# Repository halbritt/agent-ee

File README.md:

# agent-ee

**agent-ee turns a captured electronics design into a verified, native KiCad
project and a fabrication package, with tool evidence at every stage.** It is
being built as the engine of an AI-driven PCB generator: an agent and an
engineer settle requirements, parts and circuit intent, and agent-ee produces
the schematic, places and routes the board, runs the checks, and exports
Gerbers, drills, BOM and CPL. The same checks and independent-review machinery
also review and repair existing KiCad projects, which is where the project
started.

For explicit board and circuit decisions, use [design capture and compile](docs/design-compile.md), then [build run](docs/build-workflow.md). For end-user and operator guides, see the [Quickstart Guide](docs/quickstart.md), [Operator Runbook](docs/operator-runbook.md), [Architecture & Pipeline Guide](docs/architecture-pipeline.md), [Benchmarking Guide](docs/benchmarking-guide.md), and [Troubleshooting & FAQ](docs/troubleshooting-faq.md). Core terminology is documented in [GLOSSARY.md](GLOSSARY.md).

The owner's direction since 2026-10-17 is the generator
([decisions](docs/decisions.md)); the review workflow is one of its stages,
not the product. This README describes what the generator can do today and
what it cannot. The ticket-by-ticket history of implemented capabilities up to
2026-10-25 is in the [capability log](docs/capability-log.md), a frozen record.

How its placement and routing compare with stock KiCadRoutingTools on real
boards is measured in the
[matched benchmark](docs/benchmarks/krt-matched-2026-11-09.md). Its newest
"Result in brief" section is the current standing; it does not support a
general claim that agent-ee is better.

## Status at a glance (2026-11-14)

What works through the build entrypoint, `agent-ee build run`, and the synthesis entrypoint, `agent-ee design generate`:

| Stage | What runs | Demonstrated on |
| --- | --- | --- |
| Requirements & Synthesis | `design generate` turns prose requirements (`REQUIREMENTS.md`) into an `agent-ee.design/1` statement with trace citations via a subscription author seat; `build run` validates an authored spec, its byte-located requirement record and requirement-to-check map | `design generate`: led-flasher, load-switch, rs485 (benchmark r5b); `build run`: 17-part acquisition board |
| Parts | Binds authored/selected parts, captured datasheets, symbols and footprints to circuit intent; checks footprint DFM rules | acquisition board; generated r5b designs |
| Scaffold | Creates native project, board outline, stackup, rules and fixed connectors | acquisition board; generated r5b designs |
| Schematic | Emits native schematic from circuit intent, runs ERC and forward-annotates footprints | acquisition board; 130-part emitter benchmark; generated r5b designs |
| Placement and routing | Rust placement search over declared groups, fixed poses, locality and planes; routing by [kicad-route](docs/routing-adapter.md) at the commit each attempt records; native DRC and locality checks on the saved board | acquisition board; generated r5b designs; esp_prog (placement and routing only) |
| Artwork | Moves silk reference fields off conflicts under a receipt; places silkscreen labels | acquisition board; generated r5b designs |
| Package | Checks-only review (ERC, DRC, parity, interval, SPICE, DFM, assembly readiness, copper width), then Gerber/drill/BOM/CPL export bound to final board hash | acquisition board; generated r5b designs |

One real pre-authored design has completed all seven stages to an accepted package: the
17-part TPS7A20 + ADS1115 acquisition board, on 2026-10-24
([acceptance map](docs/system-acceptance.md)). In autonomous requirements-to-board
generation (`agent-ee design generate`), benchmark round r5b (2026-11-04) accepted
three of five boards (`led-flasher`, `load-switch`, `rs485`) from natural-language
requirements briefs; the two unaccepted boards (`current-monitor` and `usb-regulator`)
exposed tool defects (unpaired differential net handling, and pre-existing footprint
NPTH hole clearances) that were subsequently resolved in tooling. Subsequent
engineering reviews of the accepted boards identified design omissions (such as
unterminated bus failsafe bias and unbuffered off-board control inputs), which were
mapped to general check rules rather than board-specific fixes.

How placement and routing compare with stock KiCadRoutingTools on real boards is
measured in the [matched benchmark](docs/benchmarks/krt-matched-2026-11-09.md):
placing and routing on its own, agent-ee delivers 2 of 6 boards clean (and stock
KRT delivers 1 of 6); routing the designer's placement, the two are level.

Current pipeline capabilities and limitations:

- **Prose synthesis is provided by `agent-ee design generate`, not `build run`.**
  `agent-ee build run` requires structured JSON and Markdown inputs authored before
  the run. `agent-ee design generate` accepts prose requirements up to 32 KiB and
  queries an LLM author seat (`codex:gpt-6.1-sol:high` or `agy`) to synthesize
  `agent-ee.design/1` statements with quoted trace citations before compiling and
  building the candidate.
- **Build and routing times depend on search budgets.** Typical placement and
  routing passes require several to tens of minutes depending on board density and
  seed count; claims of "manufacturing-ready in under five minutes" do not describe
  non-trivial boards.
- **Functional-group and proximity intent are soft.** They steer the placement
  search as cost terms. Final acceptance checks declared pin locality, fixed
  connector edges, planes and native DRC; it does not check that every part
  landed in its group.
- **Engineering verification is as good as the authored map.** Only checks the
  map names are run; the mandatory set is ERC, DRC, netlist, geometry, parts
  membership, placement, envelope, fab profile, assembly readiness and package.
- **Automated testing runs on the host.** Host-native tests run via `mise` with
  Bubblewrap sandboxing; the full suite runs nightly on the host. Hosted CI
  validates commit recency rather than running tests or building images. Sample
  tables in documentation (such as the "21/25" PCBSchemaGen summary in the
  benchmarking guide) illustrate schema output formats, not verified measurements.
- **Independent AI review is not part of the build.** The package stage runs
  automated checks only. The review and campaign commands provide reviewers and
  adjudication for a candidate separately.

## How a build works

```text
spec.md + spec-record.json + requirement-map.json      (authored)
parts.json + circuit.json + layout.json + ratings.json (authored, captured sources)
envelope.json + fab-profile.json                       (authored)
placement.json + groups.json + planes.json             (authored)
        |
        v
agent-ee build run build.json --out RUN
  01 requirements  -> scope with mapped checks and accounting
  02 parts         -> bound connectivity intent and ratings receipt
  03 scaffold      -> empty native project with outline, stackup, rules, fixed parts
  04 schematic     -> .kicad_sch, ERC, netlist, footprints on the board
  05 placement-routing -> Rust placement search, kicad-route routing, saved-board DRC
  06 artwork       -> silk field relocation under receipt
  07 package       -> checks-only review, Gerbers/drills/BOM/CPL bound to board hash
```

Each stage writes a hash-bound candidate directory and a receipt. Resumption
re-checks the plan, the input source and the native tool runtime (KiCad, Python).
A changed agent-ee source does not refuse a resume; the report records it in
`tool_changes`. A `CANCEL` file stops before the next
stage. `--through STAGE` stops at a checkpoint for diagnosis. See the
[build workflow](docs/build-workflow.md) for the plan format and
[placement job](docs/placement-job.md) for search, router and budget settings.

### Core generator commands

| Command | Purpose | Reference |
| --- | --- | --- |
| `agent-ee build run PLAN` | Run the complete 7-stage generative build pipeline | [build-workflow](docs/build-workflow.md) |
| `agent-ee build review RUN` | Independently re-check completed build candidate | [build-workflow](docs/build-workflow.md) |
| `agent-ee place run CONFIG` | Execute standalone placement search and routing | [placement-job](docs/placement-job.md) |
| `agent-ee place metrics BOARD` | Evaluate native placement quality metrics and wirelengths | [placement-job](docs/placement-job.md) |
| `agent-ee parts compile ARGS` | Compile part selections and bind footprint/symbol sources | [parts-stage](docs/parts-stage.md) |
| `agent-ee design compile DESIGN` | Validate and compile typed design statement to build bundle | [design-compile](docs/design-compile.md) |
| `agent-ee design capture DESIGN` | Capture circuit and envelope into design schema | [design-compile](docs/design-compile.md) |
| `agent-ee design generate REQUIREMENTS` | Synthesize design schema statement from engineering requirements document | [design-compile](docs/design-compile.md) |
| `agent-ee design benchmark REQUIREMENTS_DIR` | Run automated benchmark suite across requirements documents | [benchmarking-guide](docs/benchmarking-guide.md) |

## Try it

The demonstrated environment is Linux with a KiCad 10.x release (including the
`pcbnew` Python bindings on the system interpreter), ngspice, Bubblewrap and
the Rust placement engine built from `crates/placement-engine`. The CLI has no
third-party Python dependencies. See [installation](docs/installation.md);
the installer links the source launcher `bin/agent-ee`, which uses
`/usr/bin/python3`. A launcher installed another way, for example as a tool
in a separate interpreter, will not find `pcbnew` and the build will fail
before its first stage.

```sh
./scripts/install.sh
agent-ee doctor
```

A review of the included RC filter runs the native checks without model calls
and takes about twenty seconds:

```sh
agent-ee review fixtures/closed-loop/control.scope.json \
  --out build/first-checks --checks-only
agent-ee inspect build/first-checks
agent-ee verify build/first-checks
```

The review command exits 1 here by design: a checks-only run leaves the
independent review unfinished even when every check passes.

A build needs an authored input bundle and a plan:

```json
{
  "schema": "agent-ee.build-plan/1",
  "source": "inputs",
  "requirements": {"map": "requirement-map.json", "record": "spec-record.json", "spec": "spec.md"},
  "parts": {"manifest": "parts.json", "circuit": "circuit.json", "layout": "layout.json"},
  "envelope": "envelope.json",
  "placement": {
    "intent": "placement.json",
    "groups": "groups.json",
    "budget_s": 1200,
    "search": {"seeds": [{"seed": 0, "start": "clustered"}], "steps_per_seed": 100000, "shortlist": 1},
    "router": {"checkout": "/opt/kicad-route"}
  },
  "verification_timeout_s": 3600
}
```

```sh
agent-ee build run build.json --out build/my-board
agent-ee build run build.json --out build/my-board --resume
agent-ee build review build/my-board --out build/my-board-review
```

`build review` independently re-checks the last completed candidate and
always reports `accepted: false`; read its `report.json`.

## The review workflow

For an existing KiCad project, `agent-ee review SCOPE` captures the design and
its requirements, runs the declared checks, asks independent circuit and
physical-design reviewers to examine the same evidence, and validates a central
adjudication of their findings. `agent-ee campaign` gives one implementation
agent a disposable copy, submits every change to fresh checks and review, and
stops on satisfied criteria, a stall or an exhausted budget. The
[recorded demonstration](evidence/README.md) shows a wrong resistor value that
passed ERC and DRC, was caught by simulation and review, and was repaired under
fresh review. See the [operator guide](docs/operator-guide.md),
[campaign guide](docs/campaign-guide.md) and
[scope reference](docs/scope-reference.md).

| Review outcome | Meaning |
| --- | --- |
| `criteria_satisfied` | Required checks and reviews completed with no accepted defects or unresolved findings. |
| `defects_or_unresolved` | Review completed with defects or open questions. |
| `incomplete` | A tool, reviewer, evidence gate, adjudication or work budget left required work unfinished. |

## Qualification designs

| Design | Role | State |
| --- | --- | --- |
| RC low-pass filter (`fixtures/rc`, `fixtures/closed-loop`) | Review and campaign demonstration; rung-1 generation driver | Reviewed, repaired and regenerated with evidence |
| Acquisition board (17 parts, TPS7A20, ADS1115, three JST connectors) | First complete build through all seven stages | Accepted package 2026-10-24; no physical validation |
| esp_prog (from KiCadRoutingTools) | Owner-named tooling test board for placement and routing | Routes clean of errors under project rules; warnings undisposed |
| Telemetry pod (fome-mc) | Target product board | Held by the owner; no attempts until tooling is accepted |
| Bounded routing articles (pairs, impedance, stripline, buses, length and delay matching, planes) | Feature qualification against stock KiCadRoutingTools on small synthetic boards | See the [acceptance map](docs/system-acceptance.md) |

## Repository map

| Path | Contents |
| --- | --- |
| `src/agent_ee/` | The CLI and all stages, checks and adapters (Python, standard library only) |
| `crates/placement-engine/` | Rust placement search engine (`agent-ee-placement`) |
| `tests/` | Unit and native integration tests; native-dependent tests skip without the toolchain, or fail under `AGENT_EE_REQUIRE_TOOLCHAIN=1` |
| `fixtures/` | RC, closed-loop, stage and fome-mc fixtures with provenance |
| `docs/` | The [manual](docs/README.md), [acceptance map](docs/system-acceptance.md), [capability log](docs/capability-log.md), qualification records and benchmarks |
| `evidence/` | Retained demonstration evidence; most run files live in the owner's private store ([relocation](docs/reproducing-evidence.md)) |
| `docker/`, `Dockerfile`, `action.yml` | Pinned toolchain image and a checks-only GitHub Action |
| `skills/agent-ee/` | Agent discovery skill for the CLI |
| `TEST_INFRA.md` | [5-Tier E2E test suite infrastructure specification](TEST_INFRA.md) |
| `GLOSSARY.md` | [Domain glossary defining 18 core circuit and placement concepts](GLOSSARY.md) |

Development:

```sh
mise tasks ls                              # the test and check entry points
mise run test:integration                  # the 5-tier end-to-end suite (tests/e2e/run_tests.sh)
mise run test:unit -- test_doctor          # the unit tests for what you changed, by module
mise run check                             # documentation, file origins, conflict markers
```

The whole unit suite takes about two hours and runs nightly; see
[AGENTS.md](AGENTS.md#working-here) for the other tasks and when to use each.

See [TEST_INFRA.md](TEST_INFRA.md) for test tier breakdowns, runner options, and coverage mappings. See the [maintainer guide](docs/maintainer-guide.md), [security](docs/security.md)
and the [enhancement roadmap](docs/enhancement-roadmap.md).

## License

agent-ee is licensed under the [MIT License](LICENSE), declared in the package
metadata. The license covers material written for agent-ee, outputs of its runs
on that material, the RC fixture copied from FOME-MC and the logic in
`src/agent_ee/checks.py` adapted from FOME-MC. The owner approved MIT for these
on 2026-10-22 ([decision](docs/decisions.md#mit-license-approved-agentee-14-2026-10-22),
relayed by the coordinator). The RC fixture embeds stock KiCad library data,
which keeps its own license.

The MIT grant does not cover files that come from other projects. These include
donor ECU design files and their libraries, stock KiCad libraries
inside the evidence archives, datasheets and fetched web pages. The
[file-origin inventory](docs/file-origins.json) classifies every tracked file by
origin, upstream license and publication status, and
[third-party origins](docs/third-party-origins.md) summarizes it for review.
Publication rights for those files are unresolved, and each origin needs an
owner decision. The public repository already contains many of them. That does
not establish a right to publish them.
The fome-mc block fixtures under `fixtures/fome-mc/` have a separate recorded
owner decision (2026-10-18). The owner holds the rights to
fome-mc. Those files are still outside the MIT grant. See their
[licence notice](fixtures/fome-mc/LICENSE-NOTICE.md).

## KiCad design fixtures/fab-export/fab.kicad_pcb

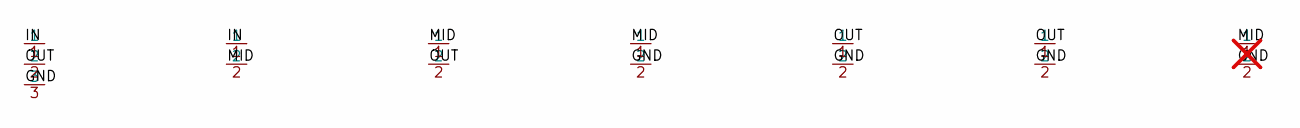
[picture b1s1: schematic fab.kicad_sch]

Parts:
C1, C2, C10: 1µF; C_1608_owned; Partnumber OFW-C-1U; LCSC C900001
C3: 100n; C_1608_owned; Partnumber OFW-C-100N; LCSC C900100; not fitted
J1: Header 3; Header_1x3_owned; Partnumber OFW-HDR3; LCSC C900030
R1: 10k; R_1608_owned; Partnumber OFW-R-10K; LCSC C900010
R2: 4.7kΩ; R_1608_owned; Partnumber OFW-R-4K7; LCSC C900047

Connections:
/GND: C1.2, C2.2, C3.2, C10.2, J1.3
/IN: J1.1, R1.1
/MID: C1.1, C3.1, R1.2, R2.1
/OUT: C2.1, C10.1, J1.2, R2.2

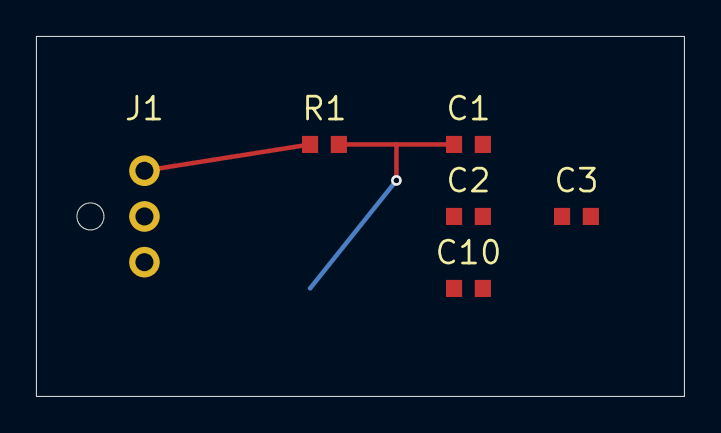
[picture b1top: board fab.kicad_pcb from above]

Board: 2 copper layers, 36.0 x 20.0 mm, 7 parts (1 on the bottom side), 4 nets.

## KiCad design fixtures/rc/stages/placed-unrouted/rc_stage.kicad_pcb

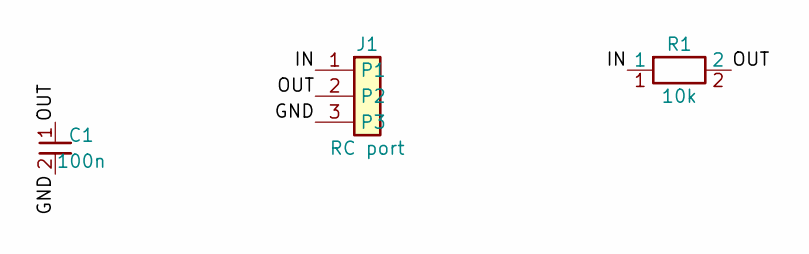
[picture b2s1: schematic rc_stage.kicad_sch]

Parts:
C1: 100n; CAP_2PAD
J1: RC port; CONN_1x3
R1: 10k; CAP_2PAD

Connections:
/GND: C1.2, J1.3
/IN: J1.1, R1.1
/OUT: C1.1, J1.2, R1.2

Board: 2 copper layers, 3 parts (0 on the bottom side), 3 nets, no tracks yet.

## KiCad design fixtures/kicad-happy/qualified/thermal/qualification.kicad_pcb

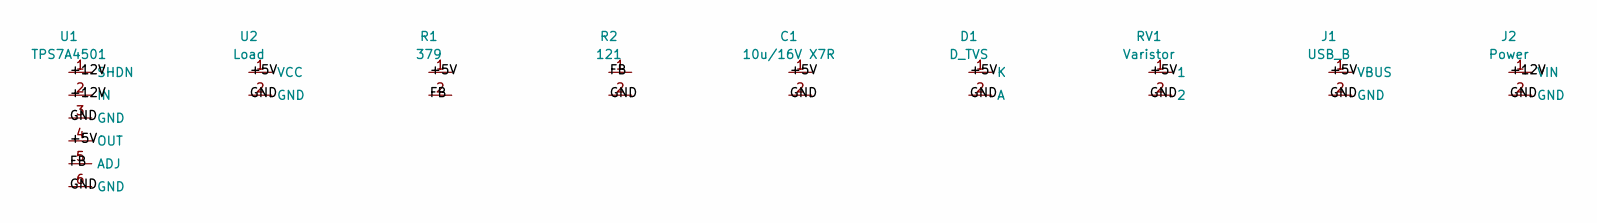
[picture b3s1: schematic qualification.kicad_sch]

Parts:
C1: 10u/16V X7R; C_0805
D1: D_TVS; D
J1: USB_B; USB
J2: Power; Conn
R1: 379; R_0805
R2: 121; R_0805
RV1: Varistor; RV
U1: TPS7A4501; SOT-23
U2: Load

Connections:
+5V: C1.1, D1.1 (K), J1.1 (VBUS), R1.1, RV1.1, U1.4 (OUT), U2.1 (VCC)
+12V: J2.1 (VIN), U1.1 (SHDN), U1.2 (IN)
FB: R1.2, R2.1, U1.5 (ADJ)
GND: C1.2, D1.2 (A), J1.2 (GND), J2.2 (GND), R2.2, RV1.2, U1.3 (GND), U1.6 (GND), U2.2 (GND)

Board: 2 copper layers, 9 parts (0 on the bottom side), 4 nets, no tracks yet.

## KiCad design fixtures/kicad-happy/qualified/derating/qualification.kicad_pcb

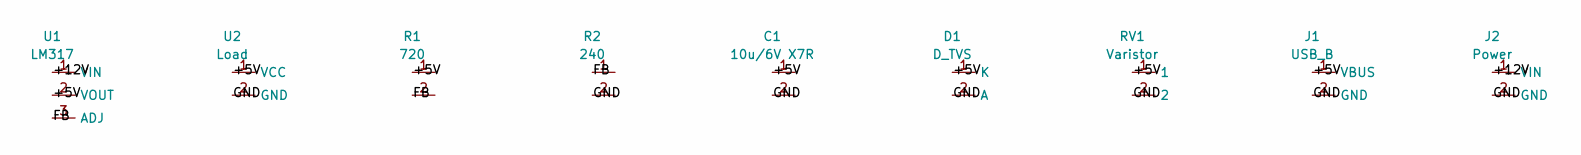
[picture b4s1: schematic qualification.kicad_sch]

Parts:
C1: 10u/6V X7R; C_0805
D1: D_TVS; D
J1: USB_B; USB
J2: Power; Conn
R1: 720; R_0805
R2: 240; R_0805
RV1: Varistor; RV
U1: LM317; SOT-223
U2: Load

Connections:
+5V: C1.1, D1.1 (K), J1.1 (VBUS), R1.1, RV1.1, U1.2 (VOUT), U2.1 (VCC)
+12V: J2.1 (VIN), U1.1 (VIN)
FB: R1.2, R2.1, U1.3 (ADJ)
GND: C1.2, D1.2 (A), J1.2 (GND), J2.2 (GND), R2.2, RV1.2, U2.2 (GND)

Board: 2 copper layers, 9 parts (0 on the bottom side), 4 nets, no tracks yet.
